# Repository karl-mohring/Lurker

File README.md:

# Lurker
Wireless sensor network for home environmental monitoring. 

# Installation

## Hardware
### Parts List
1 x Arduino Nano
1 x RF24L01+ Transceiver
1 x DS18B20 Temperature sensor
1 x DHT11 Humidity sensor
1 x BH1750FVI Illuminance sensor
1 x HC-SR501 PIR Motion sensor
2 x 4K7 Ohm resistor (1206 SMD)
2 x 390R Ohm resistor (1206 SMD)
2 x 3mm 2~3V LEDs

Optional - These components are still in development
1 x IR Blaster
1 x IR Receiver
1 x Microphone

### Circuit Board
The Lurker uses a custom PCB to connect the sensors and components together. 

### Casing
## Software

# Usage

# Network Heirarchy

# Other Info

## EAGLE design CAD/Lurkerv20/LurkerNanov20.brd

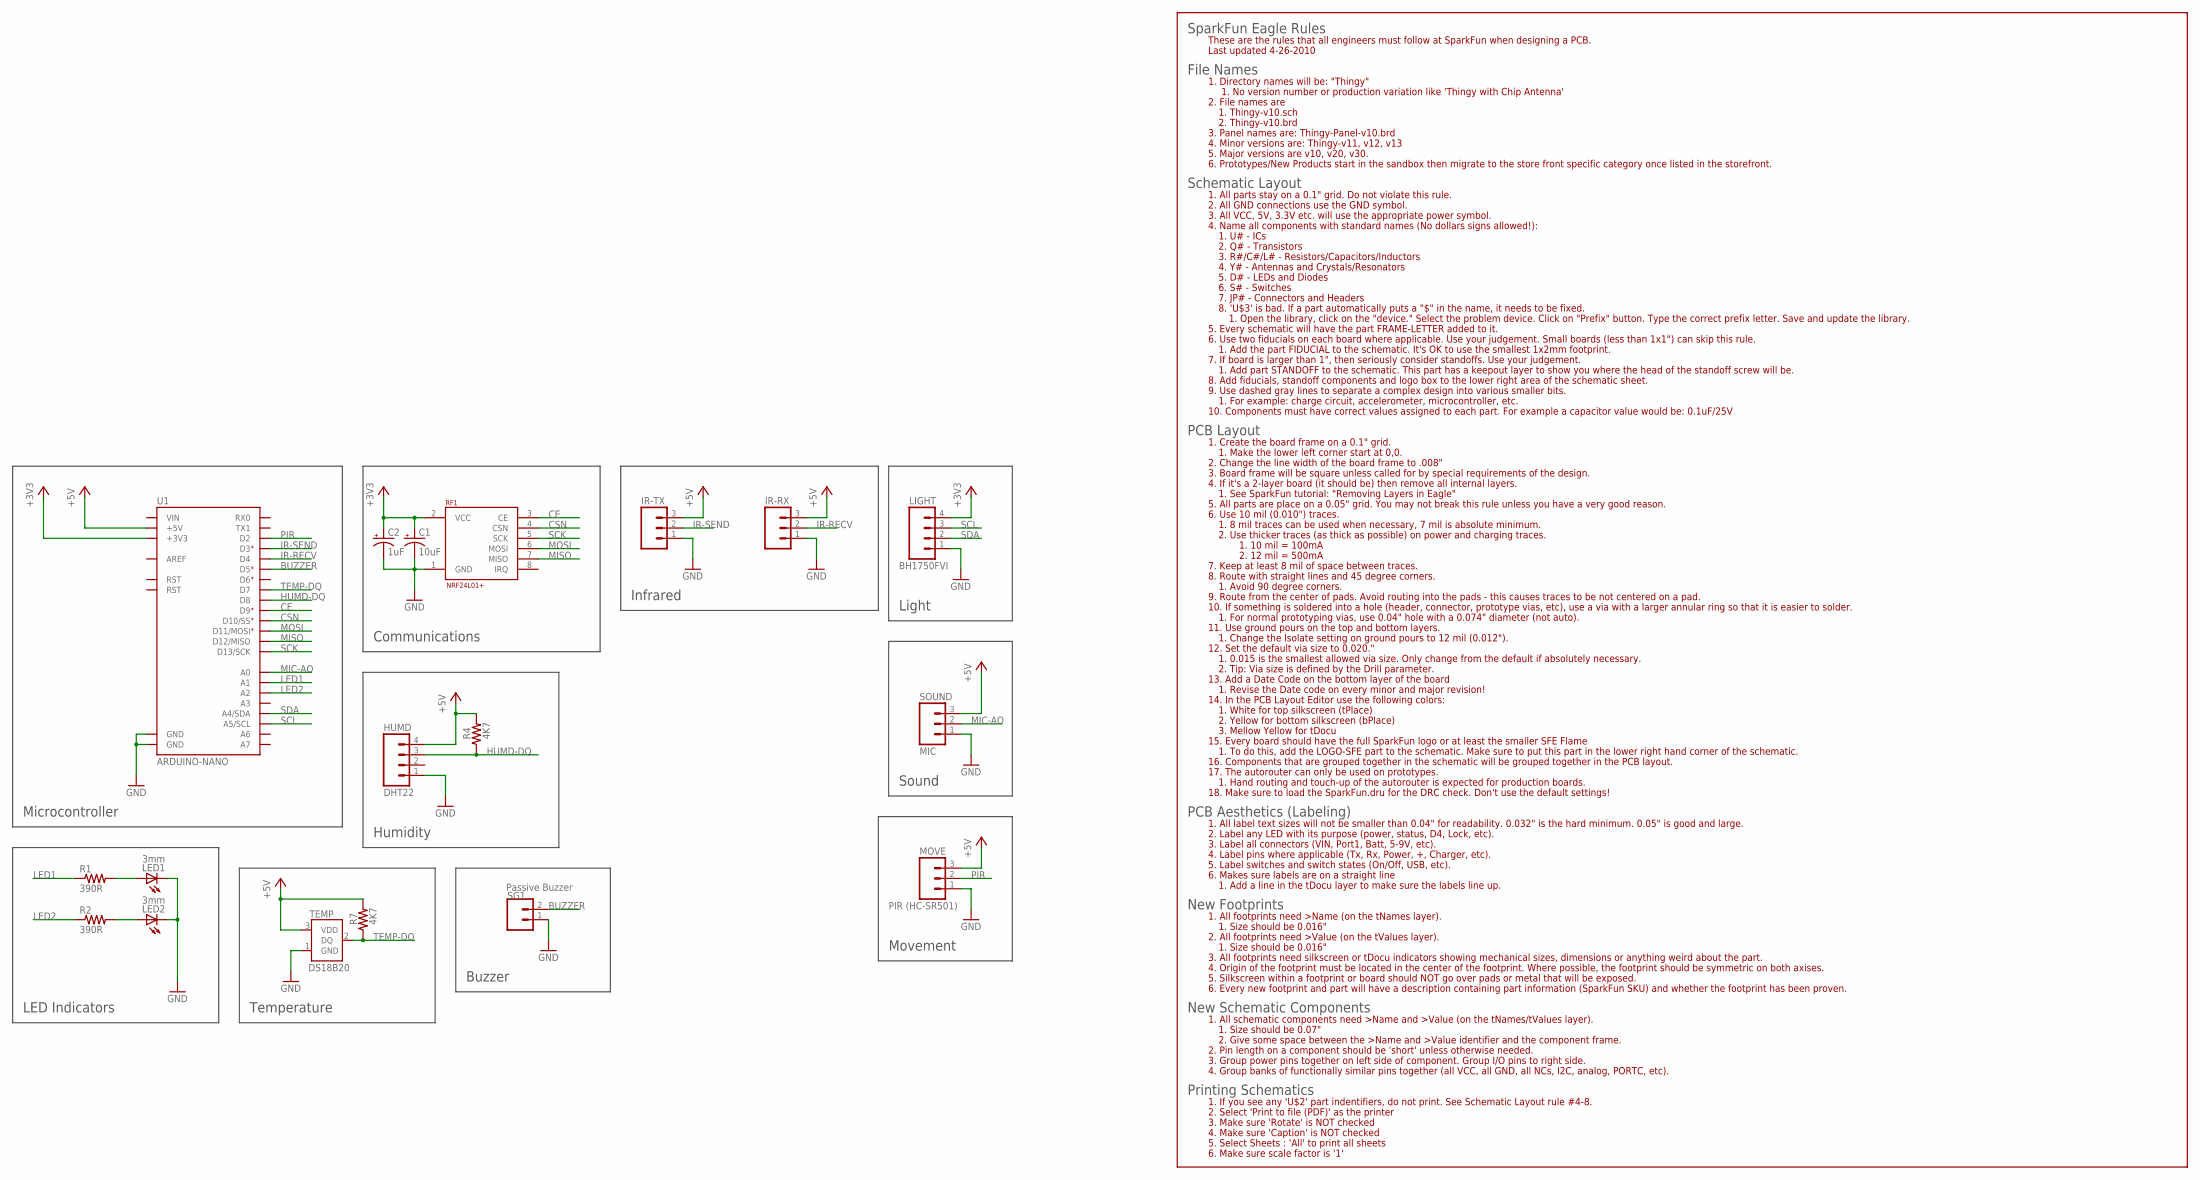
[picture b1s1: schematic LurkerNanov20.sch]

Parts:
C1: 10uF; EIA3216
C2: 1uF; EIA3216
HUMD: DHT22; 1X04
IR-RX: M03PTH; 1X03
IR-TX: M03PTH; 1X03
LED1, LED2: 3mm; LED3MM
LIGHT: BH1750FVI; 1X04
MOVE: PIR (HC-SR501); 1X03
R1, R2: 390R; 1206
R4, R7: 4K7; 1206
RF1: NRF24L01+; NRF24L01+-HEADER
SG1: Passive Buzzer; 1X02
SOUND: MIC; 1X03
TEMP: DS18B20; TO-92-AMMO
U1: ARDUINO-NANO; NANO-SHIELD

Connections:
+3V3: C1.A (+), C2.A (+), LIGHT.4, RF1.2 (VCC), U1.3V3 (+3V3)
+5V: HUMD.4, IR-RX.3, IR-TX.3, MOVE.3, R4.2, R7.2, SOUND.3, TEMP.3 (VDD), U1.5V (+5V)
BUZZER: SG1.2, U1.D5
CE: RF1.3 (CE), U1.D9
CSN: RF1.4 (CSN), U1.D10 (D10/SS)
GND: C1.C (-), C2.C (-), HUMD.1, IR-RX.1, IR-TX.1, LED1.K (C), LED2.K (C), LIGHT.1, MOVE.1, RF1.1 (GND), SG1.1, SOUND.1, TEMP.1 (GND), U1.GND@0 (GND), U1.GND@1 (GND)
HUMD-DQ: HUMD.3, R4.1, U1.D8
IR-RECV: IR-RX.2, U1.D4
IR-SEND: IR-TX.2, U1.D3
LED1: R1.1, U1.A1
LED2: R2.1, U1.A2
MIC-AO: SOUND.2, U1.A0
MISO: RF1.7 (MISO), U1.D12 (D12/MISO)
MOSI: RF1.6 (MOSI), U1.D11 (D11/MOSI)
unnamed: LED1.A, R1.2
unnamed: LED2.A, R2.2
PIR: MOVE.2, U1.D2
SCK: RF1.5 (SCK), U1.D13 (D13/SCK)
SCL: LIGHT.3, U1.A5 (A5/SCL)
SDA: LIGHT.2, U1.A4 (A4/SDA)
TEMP-DQ: R7.1, TEMP.2 (DQ), U1.D7
VIN: U1.VIN

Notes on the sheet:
Microcontroller
Temperature
Communications
Infrared
Buzzer
LED Indicators
Sound
Light
Movement
Humidity

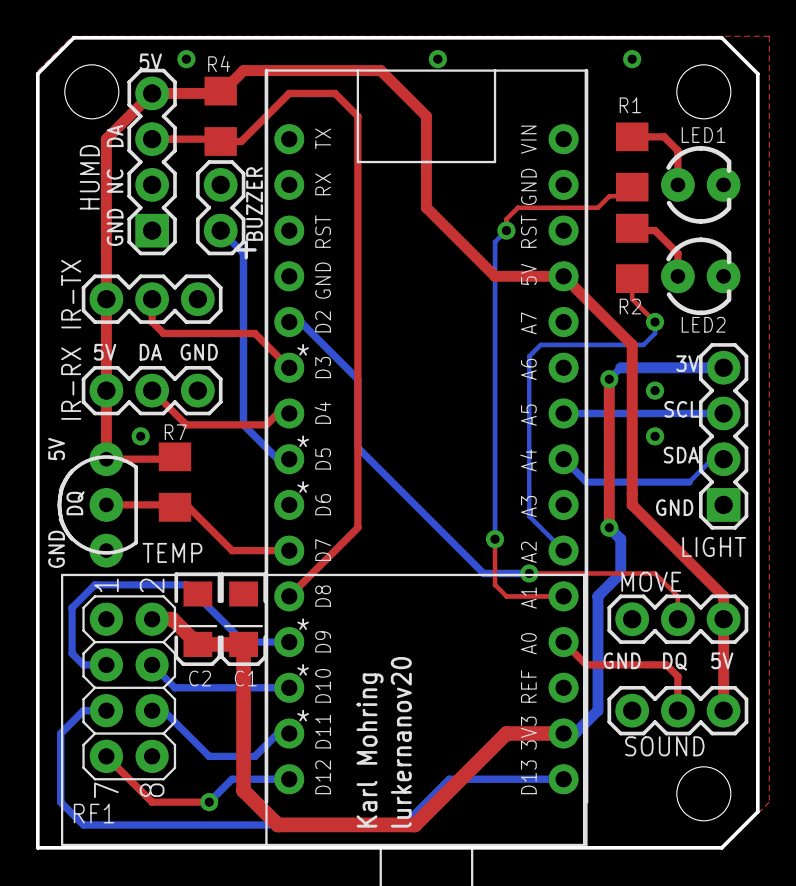
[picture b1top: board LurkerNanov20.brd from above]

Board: 2 copper layers, 40.0 x 45.0 mm, 18 parts (0 on the bottom side), 21 nets.

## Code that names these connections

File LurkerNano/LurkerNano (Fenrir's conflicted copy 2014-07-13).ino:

#include <IRremote.h>
#include <SPI.h>
#include <Wire.h>
#include <DallasTemperature.h>
#include <RF24_config.h>
#include <RF24.h>
#include <nRF24L01.h>
#include <OneWire.h>
#include <BH1750FVI.h>
#include <DHT.h>

#define UNIT_ID 0

//////////////////////////////////////////////////////////////////////////
//Communication

// RF24
#define CE_PIN 9
#define CSN_PIN 10
#define LURKER_CHANNEL 90
#define BROADCAST_PIPE 0x90909090FFLL
#define BASE_PIPE 0x9090909000LL
RF24 radio(CE_PIN,CSN_PIN);
const long unitPipe = BASE_PIPE + UNIT_ID;


/**
* Communication Protocol
*/
enum COMM_CODES{
	TIME_UPDATE = 't',
	MOTION_EVENT = 'M',
	TIME_SINCE_MOTION_EVENT = 'm',
	IR_REQUEST = 'I',
	SOUND_EVENT = 'S',
	SOUND_LEVEL_REQUEST = 's',
	BUZZ_REQUEST = 'B',
	LED_REQUEST = 'L',
	ACKNOWLEDGE_REQUEST = '+',
};


// IR
#define IR_TX_PIN 3
#define IR_RX_PIN 2
//IRsend irSend(IR_TX_PIN);


//////////////////////////////////////////////////////////////////////////
//Sensors

// Temperature
#define TEMP_PIN 4
OneWire oneWire(TEMP_PIN);
DallasTemperature tempSensor(&oneWire);

// Humidity
#define HUMD_PIN 8
#define DHT_TYPE DHT11
DHT humiditySensor(HUMD_PIN, DHT_TYPE);

// Light
BH1750FVI lightSensor;

// Sound
#define MIC_DIGITAL_PIN 6
#define MIC_ANALOG_PIN A0
#define SOUND_OVER_THRESHOLD HIGH

// Movement
#define PIR_PIN 7
#define MOVEMENT_DETECTED HIGH

//////////////////////////////////////////////////////////////////////////
// Misc

#define BUZZER_PIN 5

#define LED1_PIN A1
#define LED2_PIN A2
#define LED3_PIN A3

#define BUTTON1_PIN A6
#define BUTTON2_PIN A7

//////////////////////////////////////////////////////////////////////////

float temperature;
float humidity;
int illuminance;
int	noiseLevel;
bool noiseTriggered;
bool movementDetected;

unsigned long timeOfLastMovement;
unsigned long timeSinceLastMovement;
int dailyMovementEvents;

#define SEND_BUFFER_SIZE 32
#define RECEIVE_BUFFER_SIZE 32
char sendBuffer[SEND_BUFFER_SIZE];
char receiveBuffer[RECEIVE_BUFFER_SIZE];
byte sendBufferPutter;
byte receiveBufferGetter;
//////////////////////////////////////////////////////////////////////////

/**
* Initialization
*/
void setup()
{
	initialiseRadio();
	initialiseSensors();
}


/**
* Main Loop
*/
void loop()
{
	checkRadio();
	checkSensors();
	assembleDataPacket();
	sendDataPacket();

}

//////////////////////////////////////////////////////////////////////////


/**
* Start the RF24 radio.
* Initiliases listening pipes and allows incoming messages
*/
void initialiseRadio(){
	radio.begin();
	radio.setChannel(LURKER_CHANNEL);
	radio.setPALevel(RF24_PA_HIGH);
	
	// Start listening on unit-specific pipe
	radio.openReadingPipe(1, unitPipe);
	
	// Listen on broadcast pipe if not the base-station (UNIT 0)
	if (UNIT_ID != 0){
		radio.openReadingPipe(2, BROADCAST_PIPE);
	}
	
	radio.startListening();
}


/**
* Start up the Lurker's sensors
*/
void initialiseSensors(){
	tempSensor.begin();
	
	humiditySensor.begin();
	
	lightSensor.begin();
	lightSensor.SetMode(Continuous_H_resolution_Mode);
	
}


/**
* Check for incoming packets and act accordingly
*/
void checkRadio(){
	if (radio.available()){
		radio.read(receiveBuffer, RECEIVE_BUFFER_SIZE);
		processReceivedPacket();
	}
}


void processReceivedPacket(){
	//TODO process packets once received
	
	switch 
}


/**
* Send an acknowledgment packet to the base station
*/
void acknowledgeRequest(char c){
	radio.stopListening();
	
	radio.openWritingPipe(BASE_PIPE);
	
	
}


/**
* Insert a character into the send buffer
*/
void toSendBuffer(char c){
	// Only insert character if there is room left in the buffer
	if (sendBufferPutter < SEND_BUFFER_SIZE){
		sendBuffer[sendBufferPutter] = c;
		sendBufferPutter++;
	}
}

/**
* Insert a 16-bit integer into the buffer
*/
void toSendBuffer(int i){
	toSendBuffer(char(highByte(i)));
	toSendBuffer(char(lowByte(i)));
}


/**
* Initialise the send buffer
*/
void resetSendBuffer(){
	sendBufferPutter = 0;
}


/**
* Get the next character from the receive buffer
*/
char fromReceiveBuffer(){
	char c = receiveBuffer[receiveBufferGetter];
	
	if (receiveBufferGetter < RECEIVE_BUFFER_SIZE){
		receiveBufferGetter++;
	}
	
	return c;
}


/**
* Initialize the receive buffer by resetting the getter position
*/
void resetReceiveBuffer(){
	receiveBufferGetter = 0;
}


/**
* Obtain readings from all of the Lurker's sensors
*/
void checkSensors(){
	checkTemperature();
	checkHumidity();
	checkLight();
	checkSound();
	checkMovement();
}


/**
* Take a temperature reading.
*/
void checkTemperature(){
	tempSensor.requestTemperatures();
	temperature = floatToInt(tempSensor.getTempCByIndex(0), 2);
}


/**
* Check the relative humidity sensor.
* Output given as a percentage (float)
* The DHT11 takes up to 2 seconds to deliver a response.
*/
void checkHumidity(){
	humidity = floatToInt(humiditySensor.readHumidity(), 2);
}


/**
* Check the light level hitting the sensor.
* Values are in lux.
*/
void checkLight(){
	illuminance = lightSensor.GetLightIntensity();
}


/**
* Check if the sound level threshold has been exceeded
*/
void checkSound(){
	//TODO check if sound level threshold has been exceeded
}


/**
* Check the PIR sensor for detected movement
* The sensor will output HIGH when motion is detected.
* Output will fall back to LOW after a set delay time (adjustable on the sensor)
* The delay timer is reset with each detection; i.e. The output will be high so long as motion is detected + the delay.
*/
void checkMovement(){
	movementDetected = digitalRead(PIR_PIN);
	
	// If motion detected, reset the movement timer
	if (movementDetected == MOVEMENT_DETECTED){
		timeSinceLastMovement = 0;
		timeOfLastMovement = millis();
	}
	else{
		timeSinceLastMovement = millis() - timeOfLastMovement;
	}
}


void assembleDataPacket(){
	toSendBuffer(TEMPERATURE_DATA);
	toSendBuffer(temperature);
	
	toSendBuffer(HUMIDITY_DATA);
	toSendBuffer(humidity);
	
	toSendBuffer(LIGHT_DATA);
	toSendBuffer(illuminance);
}

/**
* Convert a floating point decimal number into an int
* The decimal is shifted prior to conversion to preserve precision, but reduce range.
* e.g. floatToInt(12.34, 2) = 1234
*
* @return decimal-shifted integer
* @param num Float number to convert
* @param decimalShift Number of decimal shifts (1-4)
*/
int floatToInt(float num, int decimalShift){
	long decimalMultiplier = 1;
	
	if(decimalShift > 0 && decimalShift < 5){
		decimalMultiplier = pow(10, decimalShift);
	}
	
	return (int)(num*decimalMultiplier);
}

void sendDataPacket(){
	radio.stopListening();
	
	radio.openWritingPipe(BASE_PIPE);
	radio.write(sendBuffer, sendBufferPutter);
	
	radio.startListening();
}

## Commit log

2014-07-14 :boom::camel: Added .gitattributes & .gitignore files
2014-07-14 Initial Push
    - Lurker Node code is complete but untested
    - Lurker Coordinator code needs some work
    - Lurker Base is completely blank
2014-07-30 Not sure
    + Filled in some coordinator code
2014-11-05 Added office lurker variant
2014-11-14 Output of Office Lurker changed to JSON
    Office lurker now uses all the correct sensors
    Data is transmitted into an easily ingestible format.
2015-01-15 Big update
    No idea what changes have been made because I've been spoiled by
    IntelliJ, and AtmelStudio is terrible in comparison...
    + Fixed LurkerNano
    - Still need to add in coordinator functions and networking
    - Serial output and control works
2015-01-15 Removed sound monitoring
2015-01-25 Save point - About to change to Command libraries
    - About to use command libraries for serial and RF24 command handling
    + Added in 3D printed case files
2015-01-26 Serial and command libraries now manage actions
2015-01-26 Ignored files
2015-01-26 Removed ignored files
2015-01-26 Updated ignore
2015-01-26 More ignores
2019-03-03 Old updates

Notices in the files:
parts and their libraries:
SparkFun-Connectors: Licensing: CC v3.0 Share-Alike You are welcome to use this library for commercial purposes.
